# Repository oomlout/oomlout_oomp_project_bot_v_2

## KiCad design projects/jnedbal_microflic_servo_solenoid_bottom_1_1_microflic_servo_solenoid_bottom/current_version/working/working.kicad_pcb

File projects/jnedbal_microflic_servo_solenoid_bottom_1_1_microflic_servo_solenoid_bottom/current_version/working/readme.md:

# microflic_servo_solenoid_bottom_1_1
 
## summary 
* id: jnedbal_microflic_servo_solenoid_bottom_1_1_microflic_servo_solenoid_bottom
* user: jnedbal
* name: microflic_servo_solenoid_bottom_1_1
* board: microflic_servo_solenoid_bottom
* repo: https://github.com/jnedbal/MicroFLiC_servo_solenoid_bottom_1_1
* src_file_repo_kicad_pcb: MicroFLiC_servo_solenoid_bottom.kicad_pcb
* src_file_repo_kicad_pcb_link: https://github.com/jnedbal/MicroFLiC_servo_solenoid_bottom_1_1/tree/master/MicroFLiC_servo_solenoid_bottom.kicad_pcb

* src_file_repo_sch: 
* src_file_repo_sch_link: https://github.com/jnedbal/MicroFLiC_servo_solenoid_bottom_1_1/tree/master/
* full details link: https://github.com/oomlout/oomlout_oomp_project_bot_v_2/tree/main/projects/jnedbal_microflic_servo_solenoid_bottom_1_1_microflic_servo_solenoid_bottom/current_version/working

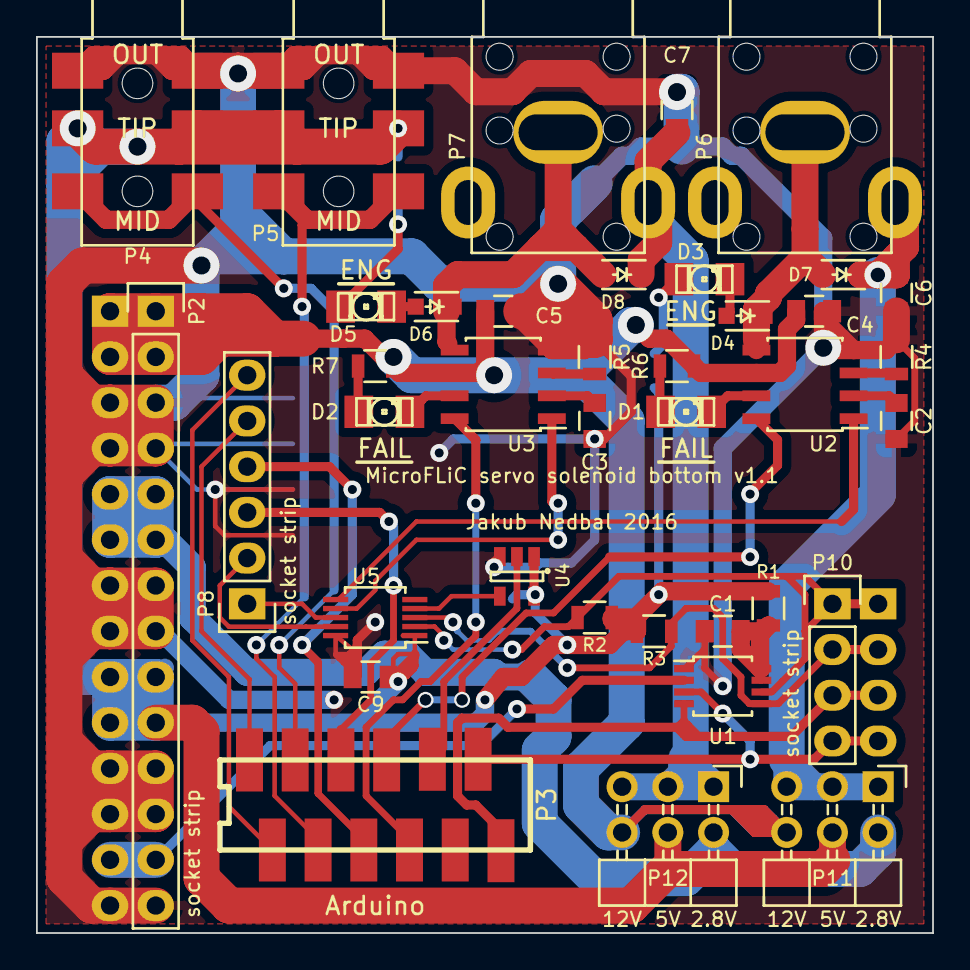
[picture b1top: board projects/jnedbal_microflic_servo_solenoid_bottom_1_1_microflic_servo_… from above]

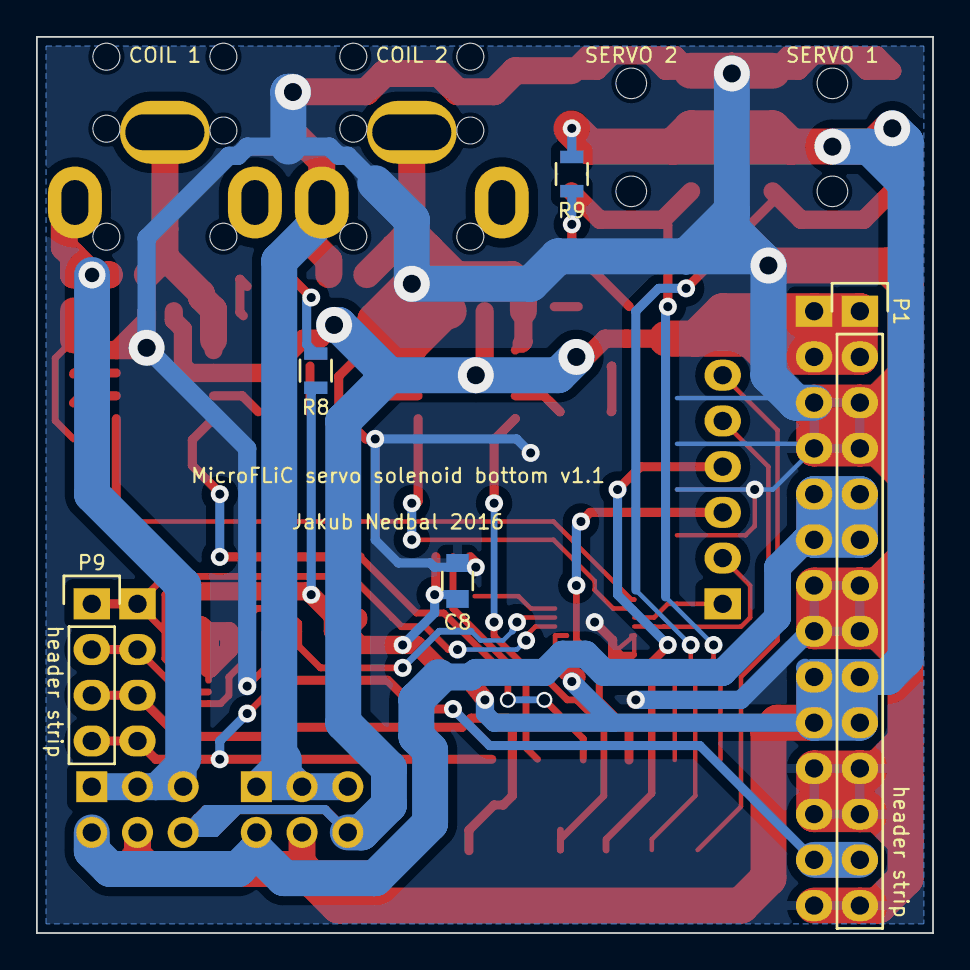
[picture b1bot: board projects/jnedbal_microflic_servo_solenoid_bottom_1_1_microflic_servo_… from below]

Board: 2 copper layers, 49.8 x 49.8 mm, 43 parts (5 on the bottom side), 40 nets.

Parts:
C1: 100p; C_0805
C2, C3: 10n; C_0805
C4, C5, C6, C7: 4u7/25V; C_0805
C8, C9: 100n; C_0805
D1, D2: LED RED; LED-1206
D3, D5: LED YELLOW; LED-1206
D4, D6, D7, D8: 1N4148; SOD-323
P1: 1x14 header strip; Pin_Header_Straight_1x14
P2: 1x14 socket strip; ESQ-114-33-G-S
P3: 12-way Micro-MaTch; 1-188275-2
P4, P5: 3.5mm jack; MJ4435-R
P6, P7: RCA jack; PSG01544
P8: 1x6 socket strip; ESQ-106-33-G-S
P9: 1x4 header strip; Pin_Header_Straight_1x04
P10: 1x4 socket strip; ESQ-104-33-G-S
P11, P12: 2x3 header strip R/A; Pin_Header_Angled_2x03
R1, R4, R5: 270k; R_0805
R2, R3: 1k5; R_0805
R6, R7: 10k; R_0805
R8, R9: 3k; R_0805
U1: PCA9306DP; TSSOP-8_3x3mm_Pitch0.65mm
U2, U3: DRV103; SOIC-8_3.9x4.9mm_Pitch1.27mm
U4: 74HCT1G125; SOT-23-5
U5: MCP4728; MSOP-10_3x3mm_Pitch0.5mm

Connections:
+2V5: P1.5, P1.6, P2.5, P2.6, P11.2, P12.2
+3V3: P1.13, P2.13, U1.2
+5VP: C8.2, C9.2, P1.9, P1.10, P2.9, P2.10, P4.3, P5.3, P11.4, P12.4, R1.1, R2.1, R3.1, R8.2, R9.2, U4.1, U4.5, U5.1
+12V: C4.2, C5.2, P1.1, P1.2, P2.1, P2.2, P11.6, P12.6, R6.2, R7.2, U2.6, U3.6
/I2C/SCL_3V3: P3.11, P9.4, P10.4, U1.3
/I2C/SCL_5V: P9.1, P10.1, R2.2, U1.6, U5.2
/I2C/SDA_3V3: P3.12, P9.3, P10.3, U1.4
/I2C/SDA_5V: P9.2, P10.2, R3.2, U1.5, U5.3
/SERVO1: P3.3, P4.2
/SERVO2: P3.4, P5.2
/SERVO3: P3.1, P8.5
/SERVO4: P3.2, P8.6
/SH3: P3.5, P8.3
/SH4: P3.6, P8.4
/shutterPWM/DA: C2.2, U2.2
/shutterPWM/DB: C3.2, U3.2
/shutterPWM/EA1: D3.2, R8.1
/shutterPWM/EA2: D3.1, D4.2
/shutterPWM/EB1: D5.2, R9.1
/shutterPWM/EB2: D5.1, D6.2
/shutterPWM/FA: D1.2, R6.1
/shutterPWM/FAIL_A: D1.1, U2.7
/shutterPWM/FAIL_B: D2.1, U3.7
/shutterPWM/FB: D2.2, R7.1
/shutterPWM/OA: R4.2, U2.3
/shutterPWM/OB: R5.2, U3.3
/shutterPWM/SH1: P3.7, U2.8
/shutterPWM/SH1_PWM: U2.1, U5.6
/shutterPWM/SH2: P3.8, U3.8
/shutterPWM/SH2_PWM: U3.1, U5.7
/shutterPWM/SH3_PWM: P8.1, U5.8
/shutterPWM/SH4_PWM: P8.2, U5.9
/shutterPWM/SHA_O/C: D4.1, D7.2, P6.1, U2.5
/shutterPWM/SHA_PWR: C6.2, D7.1, P6.2, P11.1, P11.3, P11.5
/shutterPWM/SHB_O/C: D6.1, D8.2, P7.1, U3.5
/shutterPWM/SHB_PWR: C7.2, D8.1, P7.2, P12.1, P12.3, P12.5
/shutterPWM/SH_~LDAC: P3.9, U4.2
GND: C1.2, C2.1, C3.1, C4.1, C5.1, C6.1, C7.1, C8.1, C9.1, P1.3, P1.4, P1.7, P1.8, P1.11, P1.12, P1.14, P2.3, P2.4, P2.7, P2.8, P2.11, P2.12, P2.14, P4.1, P5.1, R4.1, R5.1, U1.1, U2.4, U3.4, U4.3, U5.10
unnamed: C1.1, R1.2, U1.7, U1.8
unnamed: U4.4, U5.4

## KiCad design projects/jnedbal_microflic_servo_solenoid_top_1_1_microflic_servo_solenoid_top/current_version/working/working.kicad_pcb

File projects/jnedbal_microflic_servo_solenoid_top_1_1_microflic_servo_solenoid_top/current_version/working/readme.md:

# microflic_servo_solenoid_top_1_1
 
## summary 
* id: jnedbal_microflic_servo_solenoid_top_1_1_microflic_servo_solenoid_top
* user: jnedbal
* name: microflic_servo_solenoid_top_1_1
* board: microflic_servo_solenoid_top
* repo: https://github.com/jnedbal/MicroFLiC_servo_solenoid_top_1_1
* src_file_repo_kicad_pcb: MicroFLiC_servo_solenoid_top.kicad_pcb
* src_file_repo_kicad_pcb_link: https://github.com/jnedbal/MicroFLiC_servo_solenoid_top_1_1/tree/master/MicroFLiC_servo_solenoid_top.kicad_pcb

* src_file_repo_sch: MicroFLiC_servo_solenoid_top.sch
* src_file_repo_sch_link: https://github.com/jnedbal/MicroFLiC_servo_solenoid_top_1_1/tree/master/MicroFLiC_servo_solenoid_top.sch
* full details link: https://github.com/oomlout/oomlout_oomp_project_bot_v_2/tree/main/projects/jnedbal_microflic_servo_solenoid_top_1_1_microflic_servo_solenoid_top/current_version/working

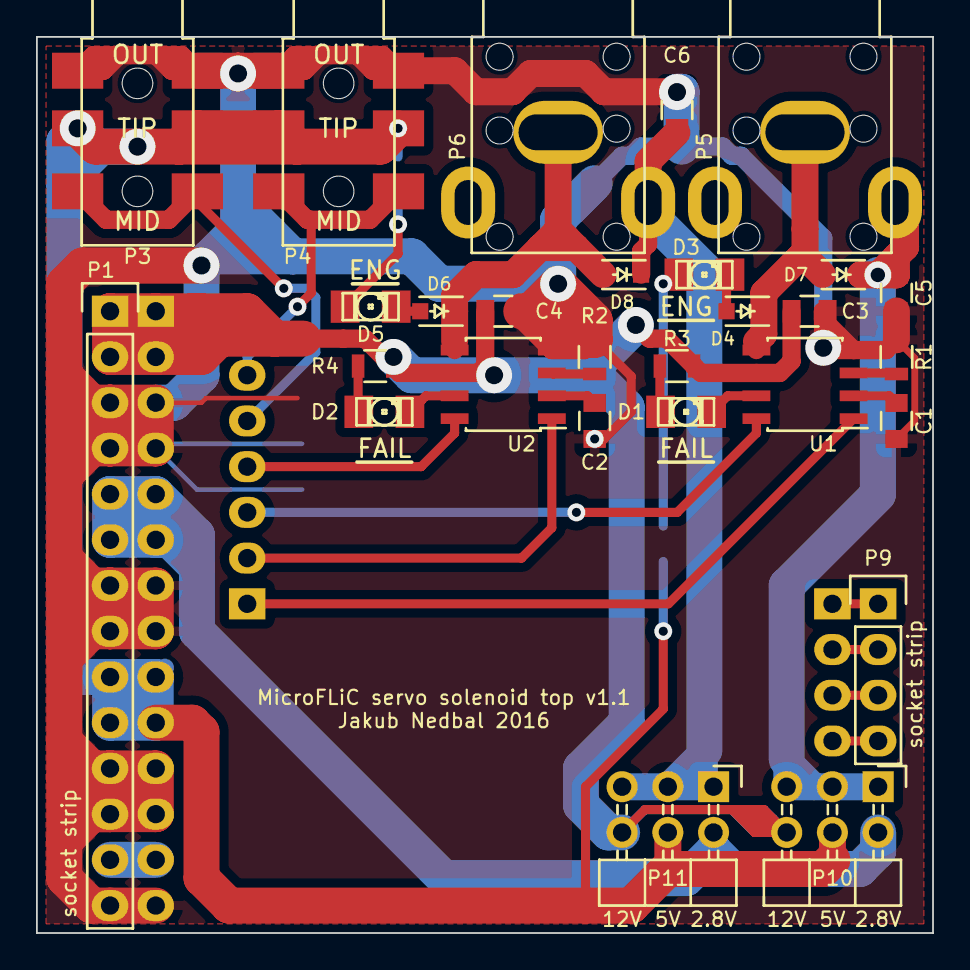
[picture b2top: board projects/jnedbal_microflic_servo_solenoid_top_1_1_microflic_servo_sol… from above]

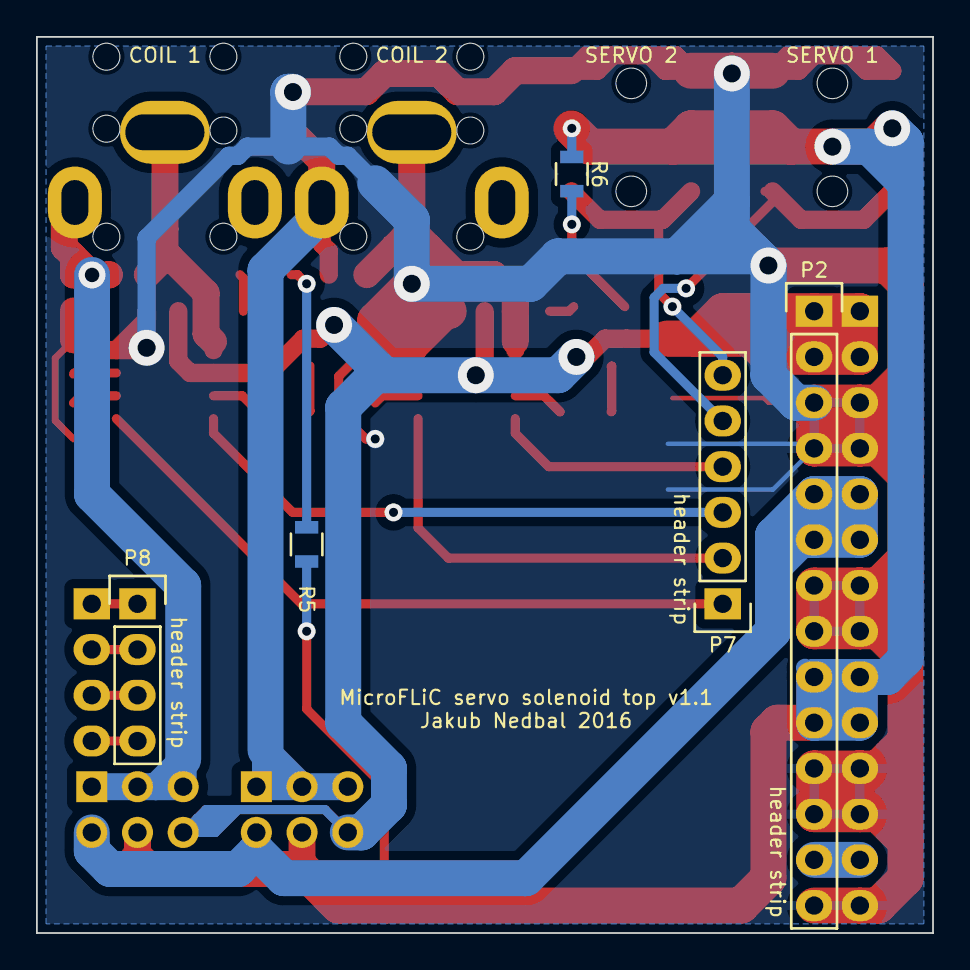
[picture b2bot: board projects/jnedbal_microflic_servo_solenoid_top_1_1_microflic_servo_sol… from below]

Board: 2 copper layers, 49.8 x 49.8 mm, 33 parts (5 on the bottom side), 31 nets.

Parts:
C1, C2: 10n; C_0805
C3, C4, C5, C6: 4u7/25V; C_0805
D1, D2: LED RED; LED-1206
D3, D5: LED YELLOW; LED-1206
D4, D6, D7, D8: 1N4148; SOD-323
P1: 1x14 socket strip; ESQ-114-33-G-S
P2: 1x14 header strip; Pin_Header_Straight_1x14
P3, P4: 3.5mm jack; MJ4435-R
P5, P6: RCA jack; PSG01544
P7: 1x6 header strip; Pin_Header_Straight_1x06
P8: 1x4 header strip; Pin_Header_Straight_1x04
P9: 1x4 socket strip; ESQ-104-33-G-S
P10, P11: 2x3 header strip R/A; Pin_Header_Angled_2x03
R1, R2: 270k; R_0805
R3, R4: 10k; R_0805
R5, R6: 3k; R_0805
U1, U2: DRV103; SOIC-8_3.9x4.9mm_Pitch1.27mm

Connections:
+2V5: P1.5, P1.6, P2.5, P2.6, P10.2, P11.2
+3V3: P1.13, P2.13
+5VP: P1.9, P1.10, P2.9, P2.10, P3.3, P4.3, P10.4, P11.4, R5.2, R6.2
+12V: C3.2, C4.2, P1.1, P1.2, P2.1, P2.2, P10.6, P11.6, R3.2, R4.2, U1.6, U2.6
/SCL_3V3: P8.4, P9.4
/SCL_5V: P8.1, P9.1
/SDA_3V3: P8.3, P9.3
/SDA_5V: P8.2, P9.2
/SERVO3: P3.2, P7.5
/SERVO4: P4.2, P7.6
/shutterPWM/DC: C1.2, U1.2
/shutterPWM/DD: C2.2, U2.2
/shutterPWM/EC1: D3.2, R5.1
/shutterPWM/EC2: D3.1, D4.2
/shutterPWM/ED1: D5.2, R6.1
/shutterPWM/ED2: D5.1, D6.2
/shutterPWM/FAIL_C: D1.1, U1.7
/shutterPWM/FAIL_D: D2.1, U2.7
/shutterPWM/FC: D1.2, R3.1
/shutterPWM/FD: D2.2, R4.1
/shutterPWM/OC: R1.2, U1.3
/shutterPWM/OD: R2.2, U2.3
/shutterPWM/SH3: P7.3, U1.8
/shutterPWM/SH3_PWM: P7.1, U1.1
/shutterPWM/SH4: P7.4, U2.8
/shutterPWM/SH4_PWM: P7.2, U2.1
/shutterPWM/SHC_O/C: D4.1, D7.2, P5.1, U1.5
/shutterPWM/SHC_PWR: C5.2, D7.1, P5.2, P10.1, P10.3, P10.5
/shutterPWM/SHD_O/C: D6.1, D8.2, P6.1, U2.5
/shutterPWM/SHD_PWR: C6.2, D8.1, P6.2, P11.1, P11.3, P11.5
GND: C1.1, C2.1, C3.1, C4.1, C5.1, C6.1, P1.3, P1.4, P1.7, P1.8, P1.11, P1.12, P1.14, P2.3, P2.4, P2.7, P2.8, P2.11, P2.12, P2.14, P3.1, P4.1, R1.1, R2.1, U1.4, U2.4

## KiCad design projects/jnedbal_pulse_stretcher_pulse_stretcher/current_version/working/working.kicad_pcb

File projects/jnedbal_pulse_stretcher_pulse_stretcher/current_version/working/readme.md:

# pulse_stretcher
 
## summary 
* id: jnedbal_pulse_stretcher_pulse_stretcher
* user: jnedbal
* name: pulse_stretcher
* board: pulse_stretcher
* repo: https://github.com/jnedbal/pulse_stretcher
* src_file_repo_kicad_pcb: pulse_stretcher.kicad_pcb
* src_file_repo_kicad_pcb_link: https://github.com/jnedbal/pulse_stretcher/tree/master/pulse_stretcher.kicad_pcb

* src_file_repo_sch: pulse_stretcher.sch
* src_file_repo_sch_link: https://github.com/jnedbal/pulse_stretcher/tree/master/pulse_stretcher.sch
* full details link: https://github.com/oomlout/oomlout_oomp_project_bot_v_2/tree/main/projects/jnedbal_pulse_stretcher_pulse_stretcher/current_version/working

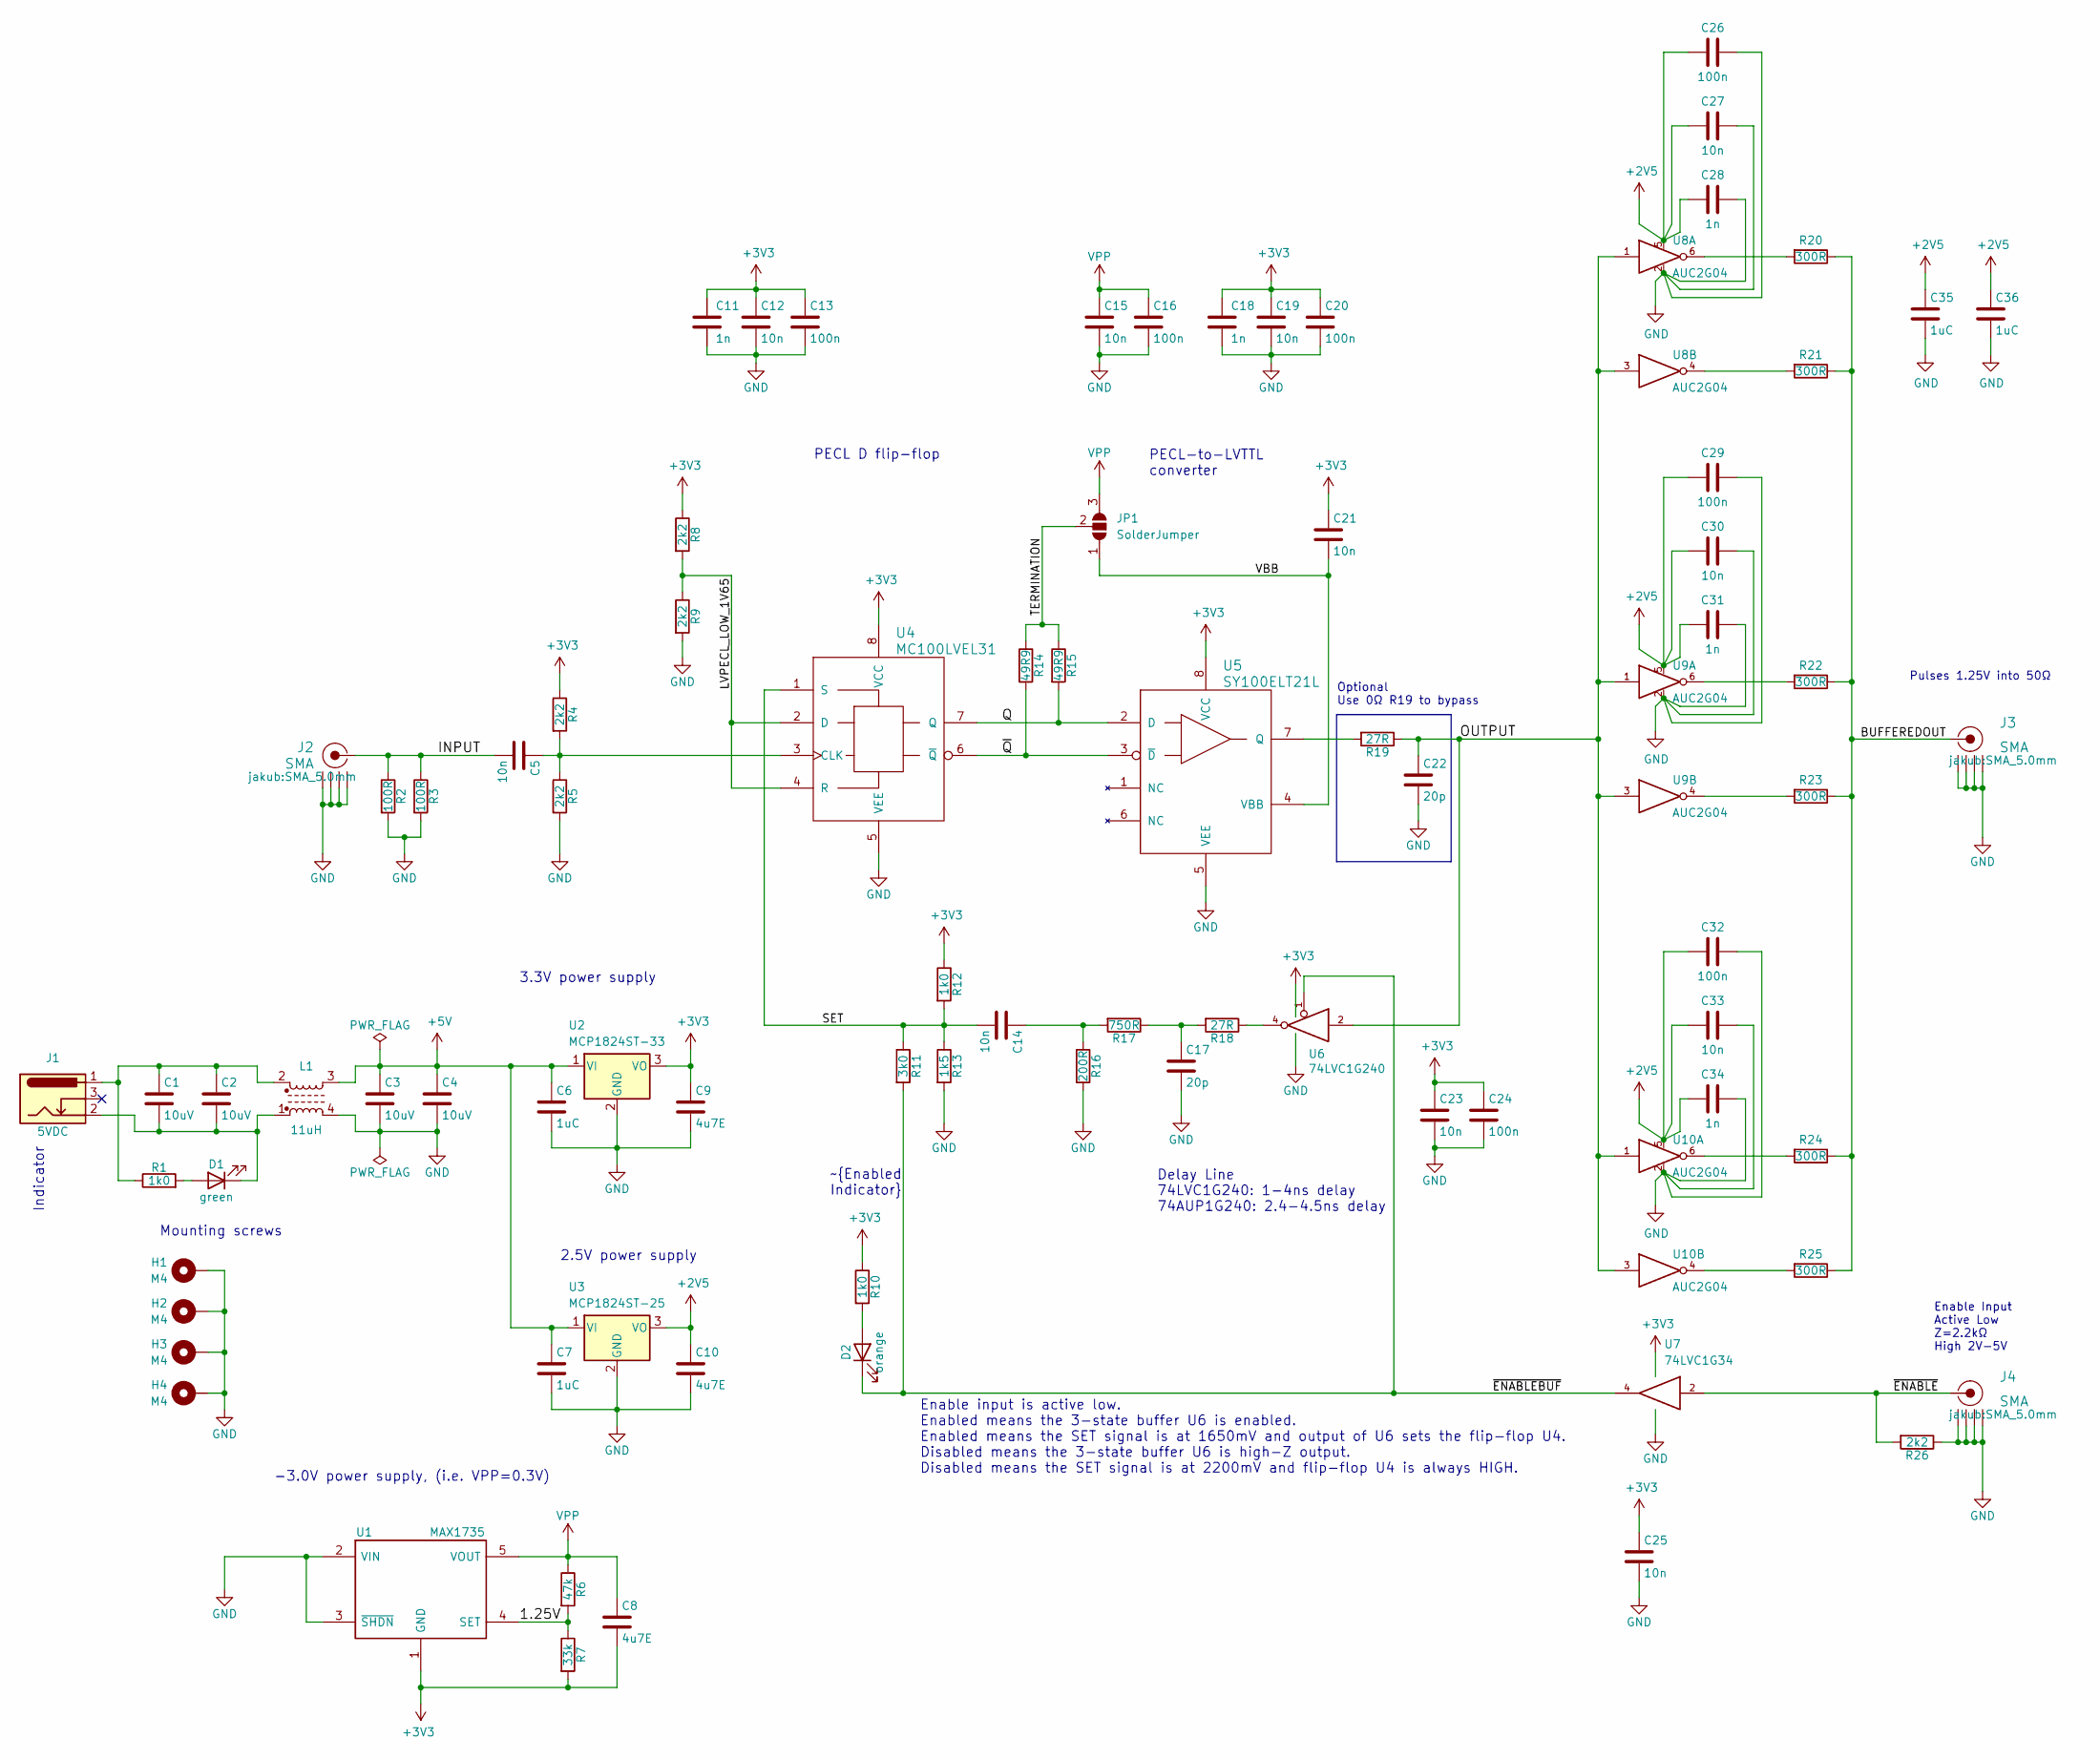
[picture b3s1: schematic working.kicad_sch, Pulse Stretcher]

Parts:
C1, C2, C3, C4: 10uV; C_1206_3216Metric; Part Number GMK316AB7106KL-TR
C5, C12, C14, C15, C19, C21, C23, C25, C27, C30, C33: 10n; C_0402_1005Metric; Part Number C0402C103K5RACTU
C6, C7, C35, C36: 1uC; C_0603_1608Metric; Part Number GRM188R61E105K
C8, C9, C10: 4u7E; C_0805_2012Metric; Part Number C2012X5R1E475K125AB
C11, C18, C28, C31, C34: 1n; C_0402_1005Metric; Part Number GRM1555C1H102JA01D
C13, C16, C20, C24, C26, C29, C32: 100n; C_0603_1608Metric; Part Number C1608X7R1H104M080AA
C17, C22: 20p; C_0603_1608Metric; Part Number MC0603N200J500CT
D1: green; LED_D3.0mm; Part Number KPT-1608SECK
D2: orange; LED_D3.0mm; Part Number KPT-1608SECK
H1, H2, H3, H4: M4; MountingHole_4.3mm_M4_Pad
J1: 5VDC; BARREL_JACK; Part Number FC681465
J2, J3, J4: SMA; SMA_5.0mm; Part Number 5-1814400-1
JP1: SolderJumper; SolderJumper-3_P1.3mm_Open_RoundedPad1.0x1.5mm
L1: 11uH; DR334A; Part Number DR334A-113BE
R1, R10, R12: 1k0; R_0603_1608Metric; Part Number RC0603FR-071KL
R2, R3: 100R; R_0603_1608Metric; Part Number MCWR06X1000FTL
R4, R5, R8, R9, R26: 2k2; R_0603_1608Metric; Part Number RC0603FR-072K2L
R6: 47k; R_0603_1608Metric; Part Number MCWR06X4702FTL
R7: 33k; R_0603_1608Metric; Part Number MCWR06X3302FTL
R11: 3k0; R_0603_1608Metric; Part Number RC0603FR-073KL
R13: 1k5; R_0603_1608Metric; Part Number RC0603FR-071K5L
R14, R15: 49R9; R_0603_1608Metric; Part Number MCWR06X49R9FTL
R16: 200R; R_0603_1608Metric; Part Number RC0603FR-07200RL
R17: 750R; R_0603_1608Metric; Part Number RC0603FR-07750RL
R18, R19: 27R; R_0603_1608Metric; Part Number MCWR06X27R0FTL
R20, R21, R22, R23, R24, R25: 300R; R_0402_1005Metric; Part Number MCWR04X3000FTL
U1: MAX1735; SOT-23-5; Part Number MAX1735EUK50+T
U2: MCP1824ST-33; SOT-223-3_TabPin2; Part Number MCP1824ST-3302E/DB
U3: MCP1824ST-25; SOT-223-3_TabPin2; Part Number MCP1824ST-2502E/DB
U4: MC100LVEL31; SOIC-8_3.9x4.9mm_P1.27mm; Part Number MC100LVEL31DG
U5: SY100ELT21L; SOIC-8_3.9x4.9mm_P1.27mm; Part Number SY100ELT21LZG
U6: 74LVC1G240; SOT-23-5; Part Number SN74LVC1G240DBVR
U7: 74LVC1G34; SOT-23-5; Part Number SN74LVC1G34DBVT
U8, U9, U10: AUC2G04; SOT-23-6_Handsoldering; Part Number SN74AUC2G04DBVR

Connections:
+2V5: C10.1, C26.2, C27.2, C28.1, C29.2, C30.2, C31.1, C32.2, C33.2, C34.1, C35.1, C36.1, U3.3 (VO), U8.5, U9.5, U10.5
+3V3: C8.2, C9.1, C11.1, C12.1, C13.1, C18.1, C19.1, C20.1, C21.1, C23.1, C24.1, C25.1, R4.1, R7.2, R8.1, R10.1, R12.1, U1.1 (GND), U2.3 (VO), U4.8 (VCC), U5.8 (VCC), U6.5 (VCC), U7.5 (VCC)
+5V: C3.1, C4.1, C6.1, C7.1, L1.3, U2.1 (VI), U3.1 (VI)
/1.25V: R6.2, R7.1, U1.4 (SET)
/BUFFEREDOUT: J3.1 (RF), R20.1, R21.1, R22.1, R23.1, R24.1, R25.1
/INPUT: C5.2, J2.1 (RF), R2.1, R3.1
/LVPECL_LOW_1V65: R8.2, R9.1, U4.2 (D), U4.4 (R)
/OUTPUT: C22.1, R19.1, U6.2, U8.1, U8.3, U9.1, U9.3, U10.1, U10.3
/Q: R15.2, U4.7 (Q), U5.2 (D)
/SET: C14.2, R11.1, R12.2, R13.1, U4.1 (S)
/TERMINATION: JP1.2 (C), R14.1, R15.1
/VBB: C21.2, JP1.1 (A), U5.4 (VBB)
/~ENABLEBUF: D2.1 (K), R11.2, U6.1, U7.4
/~ENABLE: J4.1 (RF), R26.2, U7.2
/~Q: R14.2, U4.6 (~Q), U5.3 (~D)
GND: C3.2, C4.2, C6.2, C7.2, C9.2, C10.2, C11.2, C12.2, C13.2, C15.2, C16.2, C17.2, C18.2, C19.2, C20.2, C22.2, C23.2, C24.2, C25.2, C26.1, C27.1, C28.2, C29.1, C30.1, C31.2, C32.1, C33.1, C34.2, C35.2, C36.2, H1.1, H2.1, H3.1, H4.1, J2.2 (GND1), J2.3 (GND2), J2.4 (GND3), J2.5 (GND4), J3.2 (GND1), J3.3 (GND2), J3.4 (GND3), J3.5 (GND4), J4.2 (GND1), J4.3 (GND2), J4.4 (GND3), J4.5 (GND4), L1.4, R2.2, R3.2, R5.2, R9.2, R13.2, R16.2, R26.1, U1.2 (VIN), U1.3 (~SHDN), U2.2 (GND), U3.2 (GND), U4.5 (VEE), U5.5 (VEE), U6.3 (GND), U7.3 (GND), U8.2, U9.2, U10.2
unnamed: C1.1, C2.1, J1.1, L1.2, R1.1
unnamed: C1.2, C2.2, D1.1 (K), J1.2, L1.1
unnamed: C5.1, R4.2, R5.1, U4.3 (CLK)
unnamed: C14.1, R16.1, R17.2
unnamed: C17.1, R17.1, R18.2
unnamed: D1.2 (A), R1.2
unnamed: D2.2 (A), R10.2
unnamed: R18.1, U6.4
unnamed: R19.2, U5.7 (Q)
unnamed: R20.2, U8.6
unnamed: R21.2, U8.4
unnamed: R22.2, U9.6
unnamed: R23.2, U9.4
unnamed: R24.2, U10.6
unnamed: R25.2, U10.4
VPP: C8.1, C15.1, C16.1, JP1.3 (B), R6.1, U1.5 (VOUT)

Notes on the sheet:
Enable input is active low. Enabled means the 3-state buffer U6 is enabled. Enabled means the SET signal is at 1650mV and output of U6 sets the flip-flop U4. Disabled means the 3-state buffer U6 is high-Z output. Disabled means the SET signal is at 2200mV and flip-flop U4 is always HIGH.
~{Enabled Indicator}
-3.0V power supply, (i.e. VPP=0.3V)
2.5V power supply
Enable Input Active Low Z=2.2kΩ High 2V-5V
Optional Use 0Ω R19 to bypass
PECL-to-LVTTL converter
PECL D flip-flop
Mounting screws
Delay Line 74LVC1G240: 1-4ns delay 74AUP1G240: 2.4-4.5ns delay
3.3V power supply
Pulses 1.25V into 50Ω
Indicator

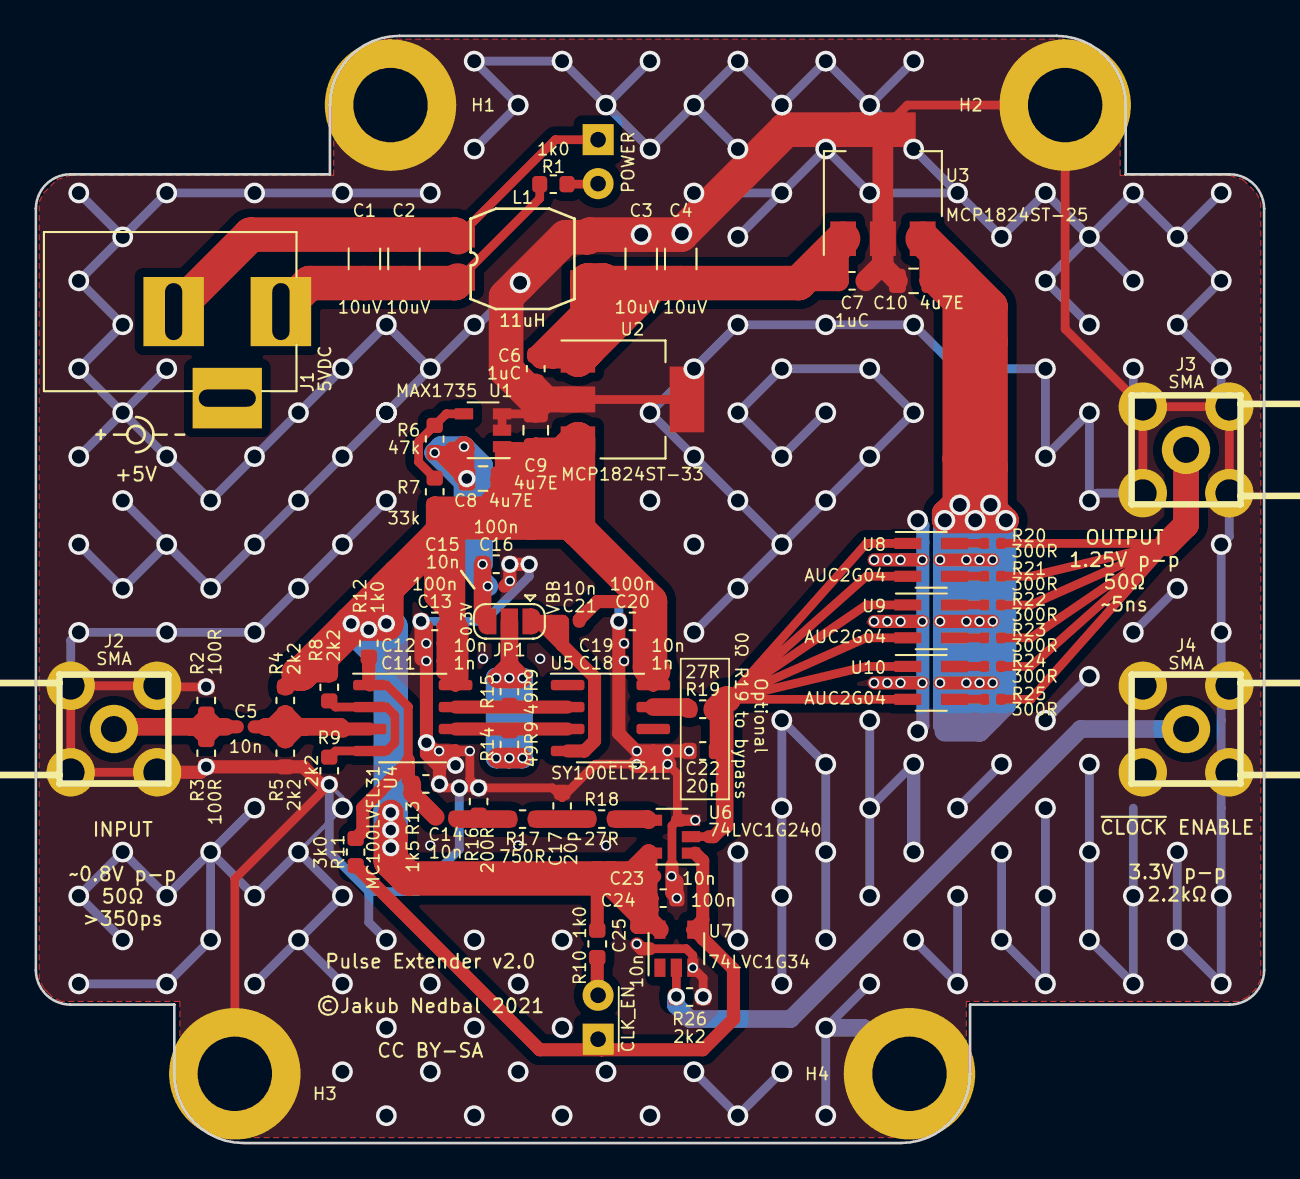
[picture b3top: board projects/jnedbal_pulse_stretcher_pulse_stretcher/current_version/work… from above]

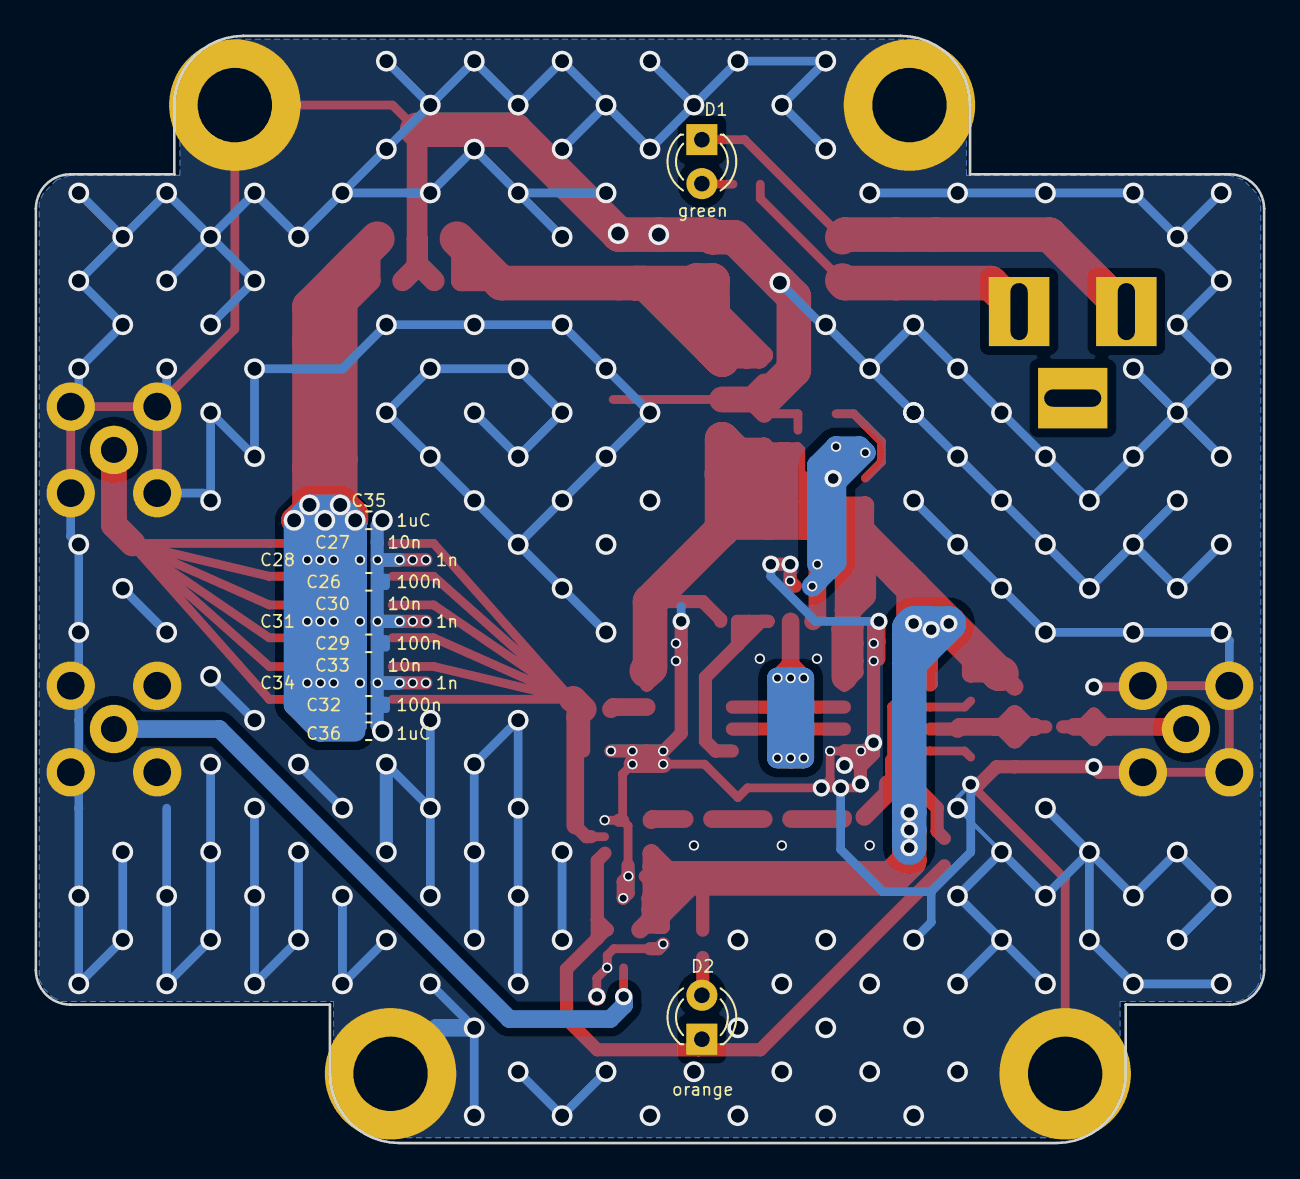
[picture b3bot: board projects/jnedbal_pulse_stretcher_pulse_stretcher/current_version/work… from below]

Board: 2 copper layers, 71.0 x 64.0 mm, 84 parts (13 on the bottom side), 32 nets.

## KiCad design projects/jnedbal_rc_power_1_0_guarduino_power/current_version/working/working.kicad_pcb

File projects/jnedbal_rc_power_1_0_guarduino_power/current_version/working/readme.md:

# rc_power_1_0
 
## summary 
* id: jnedbal_rc_power_1_0_guarduino_power
* user: jnedbal
* name: rc_power_1_0
* board: guarduino_power
* repo: https://github.com/jnedbal/RC_power_1_0
* src_file_repo_kicad_pcb: guarduino_power.kicad_pcb
* src_file_repo_kicad_pcb_link: https://github.com/jnedbal/RC_power_1_0/tree/master/guarduino_power.kicad_pcb

* src_file_repo_sch: guarduino_power.sch
* src_file_repo_sch_link: https://github.com/jnedbal/RC_power_1_0/tree/master/guarduino_power.sch
* full details link: https://github.com/oomlout/oomlout_oomp_project_bot_v_2/tree/main/projects/jnedbal_rc_power_1_0_guarduino_power/current_version/working

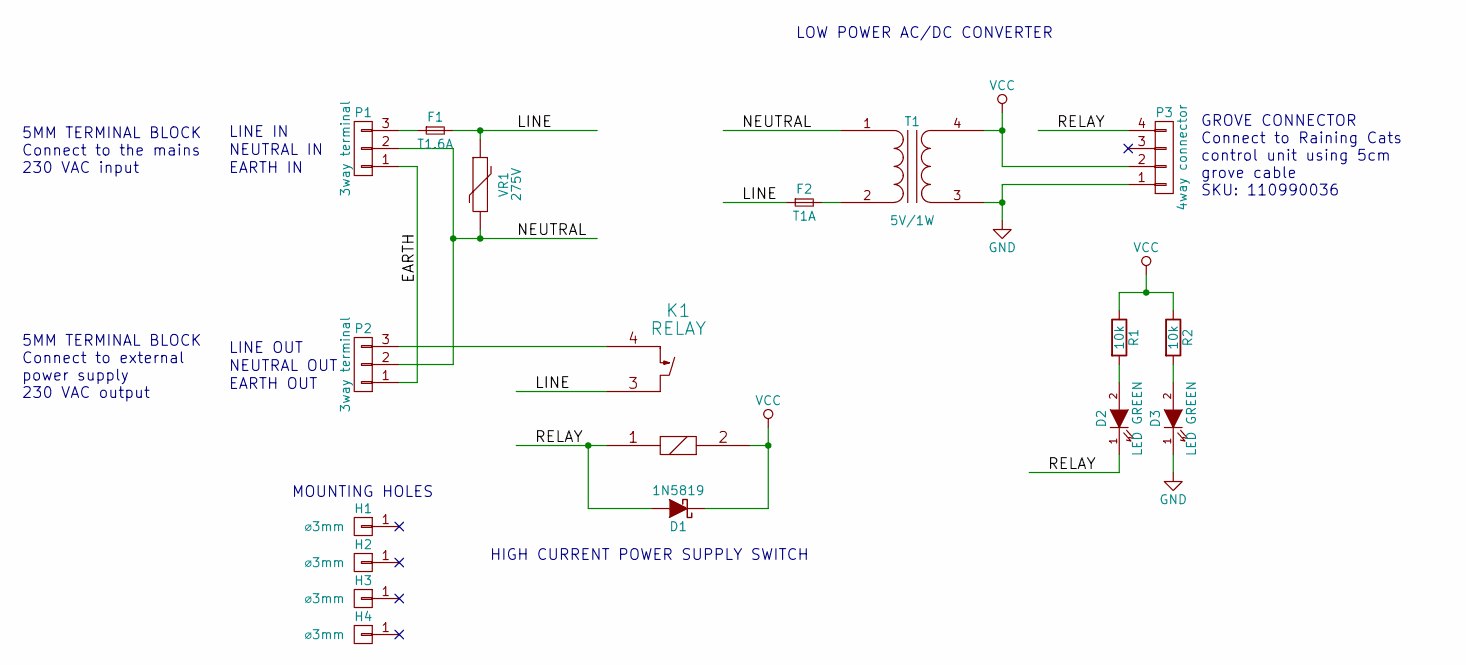
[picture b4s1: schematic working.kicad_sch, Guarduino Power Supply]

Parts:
D1: 1N5819; SOD-123; Part Number 1N5819HW-7-F
D2, D3: LED GREEN; LED_0603; Part Number 19-217-G7C-AN1P2-3T
F1: T1.6A; Fuseholder5x20_horiz_open_Schurter_0031_8201; Part Number 0031.8201
F2: T1A; Fuseholder5x20_horiz_open_Schurter_0031_8201; Part Number 0031.8201
H1, H2, H3, H4: ⌀3mm; MountingHole_3.2mm_M3
K1: RELAY; PCNrelay; Part Number PCN-105D3MHZ
P1, P2: 3way terminal; TerminalBlock_Pheonix_MKDS1.5-3pol; Part Number 22-23-2031
P3: 4way connector; JST_PH_04way_vert; Part Number 1125S-4P
R1, R2: 10k; R_0603; Part Number RC0603FR-0710KL
T1: 5V/1W; RAC01-02; Part Number RAC01-05SC
VR1: 275V; RV_Disc_D15.5_W5_P7.5; Part Number B72214S0271K101

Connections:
/EARTH: P1.1, P2.1
/LINE: F1.2, F2.1, K1.3, VR1.1
/NEUTRAL: P1.2, P2.2, T1.1 (AA), VR1.2
/RELAY: D1.2 (A), D2.1 (K), K1.1, P3.4
GND: D3.1 (K), P3.1, T1.3 (SA)
unnamed: D2.2 (A), R1.2
unnamed: D3.2 (A), R2.2
unnamed: F1.1, P1.3
unnamed: F2.2, T1.2 (AB)
unnamed: K1.4, P2.3
VCC: D1.1 (K), K1.2, P3.2, R1.1, R2.1, T1.4 (SB)

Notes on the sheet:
EARTH OUT
GROVE CONNECTOR Connect to Raining Cats control unit using 5cm grove cable SKU: 110990036
NEUTRAL IN
5MM TERMINAL BLOCK Connect to the mains 230 VAC input
EARTH IN
5MM TERMINAL BLOCK Connect to external power supply 230 VAC output
MOUNTING HOLES
LOW POWER AC/DC CONVERTER
NEUTRAL OUT
LINE IN
LINE OUT
HIGH CURRENT POWER SUPPLY SWITCH

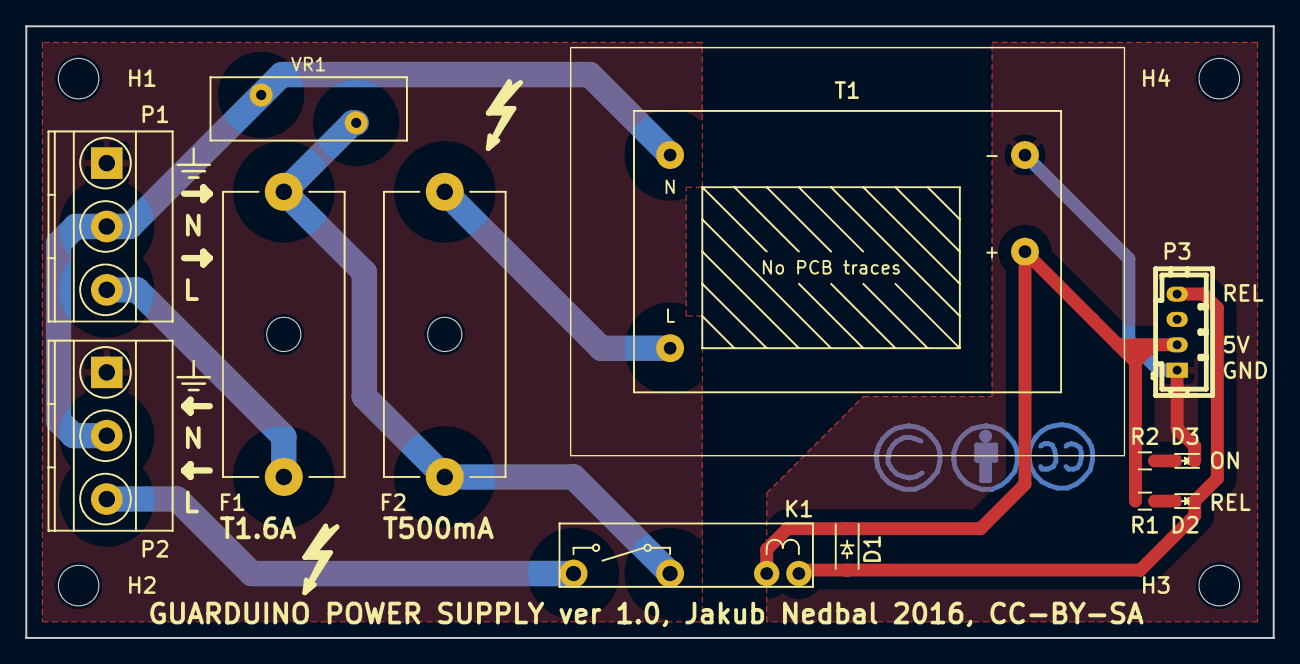
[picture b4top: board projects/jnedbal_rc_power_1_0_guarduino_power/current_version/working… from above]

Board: 2 copper layers, 98.4 x 48.3 mm, 17 parts (0 on the bottom side), 11 nets.

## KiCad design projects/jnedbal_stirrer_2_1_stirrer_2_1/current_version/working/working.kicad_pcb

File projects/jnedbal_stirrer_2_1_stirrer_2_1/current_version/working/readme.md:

# stirrer_2_1
 
## summary 
* id: jnedbal_stirrer_2_1_stirrer_2_1
* user: jnedbal
* name: stirrer_2_1
* board: stirrer_2_1
* repo: https://github.com/jnedbal/stirrer_2_1
* src_file_repo_kicad_pcb: stirrer_2_1.kicad_pcb
* src_file_repo_kicad_pcb_link: https://github.com/jnedbal/stirrer_2_1/tree/master/stirrer_2_1.kicad_pcb

* src_file_repo_sch: 
* src_file_repo_sch_link: https://github.com/jnedbal/stirrer_2_1/tree/master/
* full details link: https://github.com/oomlout/oomlout_oomp_project_bot_v_2/tree/main/projects/jnedbal_stirrer_2_1_stirrer_2_1/current_version/working

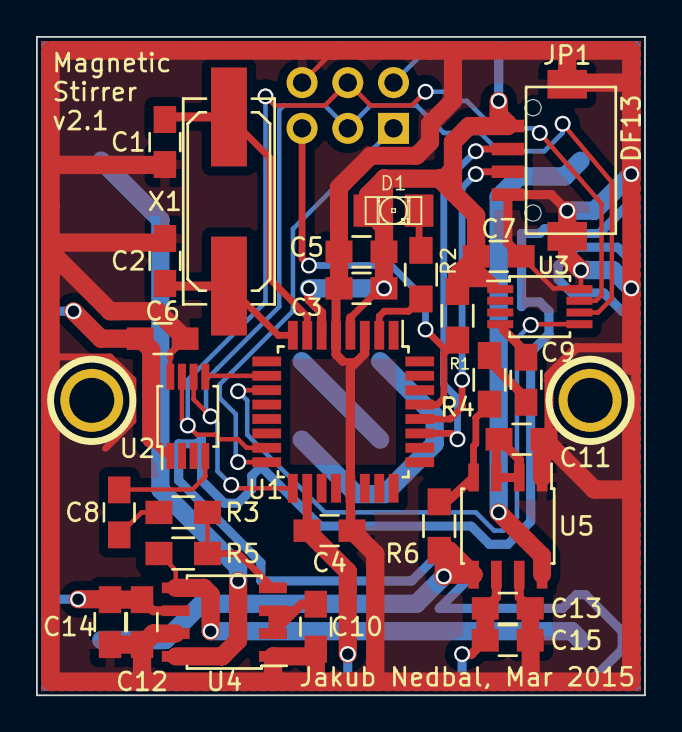
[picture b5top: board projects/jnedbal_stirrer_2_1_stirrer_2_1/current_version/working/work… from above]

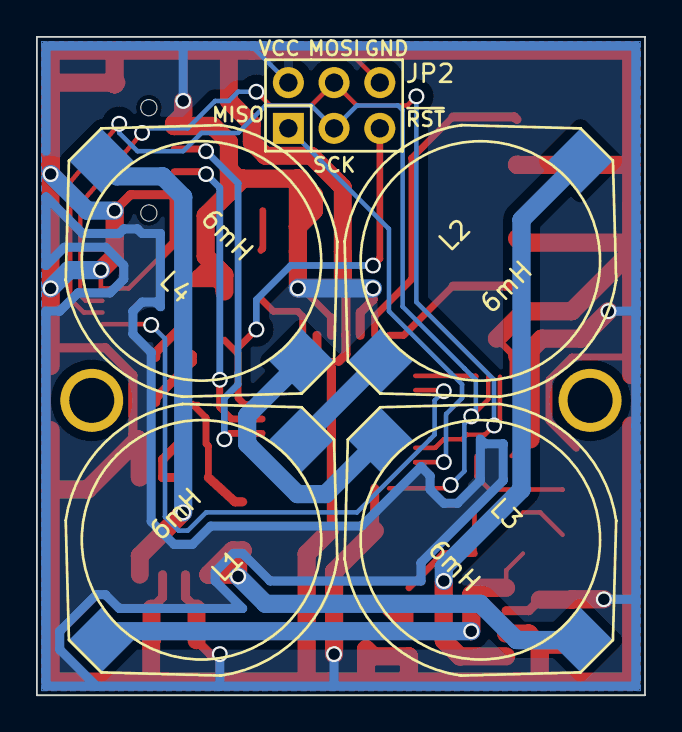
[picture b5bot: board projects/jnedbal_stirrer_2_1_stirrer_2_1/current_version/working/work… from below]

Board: 2 copper layers, 33.8 x 36.6 mm, 36 parts (5 on the bottom side), 28 nets.

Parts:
C1, C2: 18p; C_0805_HandSoldering
C3, C4, C6, C7, C12, C13: 100n; C_0805_HandSoldering
C5, C8, C9, C14, C15: 10u; C_0805_HandSoldering
C10, C11: 470n; C_0805_HandSoldering
D1: LED 1206 yel; LED-1206
JP1: DF13; DF13-4P-1.25H
JP2: CONN_3X2; Pin_Header_Straight_2x03
L1, L2, L3, L4: 6mH; 6mH_coil
P1, P2: CONN_1; 1pin
R1: 10k; R_0805_HandSoldering
R2: 470R; R_0805_HandSoldering
R3, R4: 33k; R_0805_HandSoldering
R5, R6: 22k; R_0805_HandSoldering
U1: ATMEGA328P; TQFP-32_7x7mm_Pitch0.8mm
U2, U3: DAC101S101; MSOP-8_3x3mm_Pitch0.65mm
U4, U5: TPA301; SOIC-8_3.9x4.9mm_Pitch1.27mm
X1: 8.000MHz; Q_49U3HMS

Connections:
/MISO: JP2.1, U1.16
/RESET: JP2.5, R1.2, U1.29
/powerModule_2_1/AIN1: C8.2, R3.1
/powerModule_2_1/AIN2: C9.2, R4.1
/powerModule_2_1/DACOUT1: C8.1, U2.4
/powerModule_2_1/DACOUT2: C9.1, U3.4
/powerModule_2_1/IN1+: C10.1, U4.2, U4.3
/powerModule_2_1/IN1-: R3.2, R5.1, U4.4
/powerModule_2_1/IN2+: C11.1, U5.2, U5.3
/powerModule_2_1/IN2-: R4.2, R6.1, U5.4
/powerModule_2_1/L12_VO+: L1.1, R5.2, U4.5
/powerModule_2_1/L12_VO-: L2.1, U4.8
/powerModule_2_1/L34_VO+: L3.1, R6.2, U5.5
/powerModule_2_1/L34_VO-: L4.1, U5.8
/powerModule_2_1/MOSI: JP2.4, U1.15, U2.7, U3.7
/powerModule_2_1/SCK: JP2.3, U1.17, U2.6, U3.6
/powerModule_2_1/~CS_DAC1: U1.10, U2.5
/powerModule_2_1/~CS_DAC2: U1.11, U3.5
GND: C1.2, C2.2, C3.2, C4.2, C5.2, C6.2, C7.2, C10.2, C11.2, C12.2, C13.2, C14.2, C15.2, JP1.4, JP1.5, JP1.6, JP2.6, U1.3, U1.5, U1.21, U2.8, U3.8, U4.1, U4.7, U5.1, U5.7
unnamed: C1.1, U1.7, X1.1
unnamed: C2.1, U1.8, X1.2
unnamed: D1.2, R2.1
unnamed: JP1.2, U1.27
unnamed: JP1.3, U1.28
unnamed: L1.2, L2.2
unnamed: L3.2, L4.2
unnamed: R2.2, U1.2
VCC: C3.1, C4.1, C5.1, C6.1, C7.1, C12.1, C13.1, C14.1, C15.1, D1.1, JP1.1, JP2.2, R1.1, U1.4, U1.6, U1.18, U2.1, U3.1, U4.6, U5.6

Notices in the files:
projects/jnedbal_pulse_stretcher_pulse_stretcher/current_version/working/working.kicad_pcb:
©Jakub Nedbal 2021
CC BY-SA
projects/jnedbal_pulse_stretcher_pulse_stretcher/current_version/working/working.kicad_sch:
Creative Commons Attribution-ShareAlike 4.0 International License
This work is licensed under a
projects/jnedbal_rc_power_1_0_guarduino_power/current_version/working/working.kicad_pcb:
License: CC-BY-SA
GUARDUINO POWER SUPPLY ver 1.0, Jakub Nedbal 2016, CC-BY-SA
projects/joanthespark_poepi_hardware_pizero_poe/current_version/working/working.kicad_pcb:
License: CERN OHL V1.2
